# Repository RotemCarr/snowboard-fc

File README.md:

# Snowboard

Snowboard is a custom RP2350A flight controller, built to replace the flight controller in a SpeedyBee F405 V4 stack and drive its 4-in-1 ESC. This repository holds everything for it: the KiCad hardware project, the Zephyr board definition, and the firmware.

| | |
| --- | --- |
| Hardware | Rev 3, ordered from JLCPCB (fabrication and full assembly) |
| Firmware | Snowboard Rev 3 board definition (see below) |
| Zephyr | v4.4.2 |
| Hardware spec | [RFC 0001 / SNB-HW-001](docs/rfcs/0001-flight-controller-hardware.md) |
| Firmware architecture | [RFC 0002](docs/rfcs/0002-firmware-architecture.md) |

## Repository layout

```
snowboard-fc/
├── west.yml                # west manifest: pins Zephyr and its modules
├── zephyr/module.yml       # registers this repo as a Zephyr module
├── boards/snowboard/       # Zephyr board definition (snowboard/rp2350a/m33)
├── app/                    # firmware application (becomes apps/fc, RFC 0002 §2.2)
├── hardware/               # KiCad project, fab outputs, pin map, schematic PDF
└── docs/rfcs/              # design records
```

RFC 0002 adds `apps/bringup/` (self-test firmware), `drivers/` (DShot, CRSF), `dts/bindings/` and `lib/fc/` (flight logic) as they are written.

## Getting started

### Prerequisites

- [Zephyr's host dependencies](https://docs.zephyrproject.org/latest/develop/getting_started/index.html) and the Zephyr SDK
- `west` (`pip install west`)

### Set up a workspace

This repository is the manifest of a west workspace. Zephyr and its modules are fetched next to it and are not part of the repository.

```sh
west init -m https://github.com/RotemCarr/snowboard-fc.git snowboard-workspace
cd snowboard-workspace
west update
pip install -r zephyr/scripts/requirements.txt
west zephyr-export
```

The result:

```
snowboard-workspace/
├── snowboard-fc/     # this repository
├── zephyr/
├── modules/
└── build/
```

### Build

From the workspace root:

```sh
west build -b snowboard/rp2350a/m33 snowboard-fc/apps/fc
```

### Flash

Hold BOOTSEL while connecting USB, so the RP2350 mounts as a drive, then:

```sh
west flash -r uf2
```

With a Raspberry Pi Debug Probe on the SWD connector (J4), use `west flash -r probe-rs` or `west flash -r openocd`; `west debug` works the same way.

The board definition in `boards/snowboard/` describes Snowboard Rev 3 itself, following `hardware/docs/pinmap.md`: the ICM-42688 IMU on SPI0, the CRSF receiver on UART0 (J3), the battery, current and RSSI ADC channels, the status LED, buzzer and RGB LED, and the aux UART (PIO2) and I2C pads. The console is on USB (CDC ACM). DShot, the CRSF receiver node and flash partitions are still TODO in `snowboard.dtsi`; they are added with their drivers.

## Testing

Unit tests live in `tests/` and run on Zephyr's `native_sim` board, built with the host GCC, so no Zephyr SDK or hardware is needed. The `Dockerfile` provides the environment for this.

### Build the image

From the workspace root:

```sh
docker build -t snowboard-sim \
  --build-arg ZEPHYR_REF=v4.5.0 \
  --build-arg UID=$(id -u) --build-arg GID=$(id -g) \
  snowboard-fc
```

`ZEPHYR_REF` selects which Zephyr revision's Python requirements are installed and should match the revision in `west.yml`. `UID` and `GID` make files written to the mounted workspace belong to you.

### Run the tests

Start a container from the workspace root, which is mounted at `/workspace`. The named `snowboard-ccache` volume keeps the compiler cache between runs:

```sh
docker run --rm -it \
  -v "$PWD":/workspace \
  -v snowboard-ccache:/home/dev/.ccache \
  snowboard-sim
```

Inside the container, run every test suite with Twister:

```sh
west twister -T snowboard-fc/tests -p native_sim/native/64 --inline-logs
```

Twister finds each suite by its `testcase.yaml`, builds it, runs it and reports the results. To run one scenario, select it by the name in its `testcase.yaml`:

```sh
west twister -T snowboard-fc/tests -p native_sim/native/64 -s lib.fc.arming
```

Results are written to `twister-out/` in the workspace root; earlier runs are kept as `twister-out.1`, `twister-out.2` and so on. `twister-out/twister.json` holds the full report, and each suite's build directory, including its `handler.log`, is under `twister-out/`.

To browse the results, run `tools/twister-dashboard/serve.sh` on the host from the workspace root. It opens a local dashboard of every `twister-out*` run.

## Hardware

Open `hardware/snowboard_fc.kicad_pro` in KiCad 7 or newer. `hardware/README.md` covers the board, its RP2350 core (copied from Raspberry Pi's Minimal design), ordering, and planned changes for the next revision.

| File | Content |
| --- | --- |
| `hardware/docs/schematic-rev3.pdf` | All schematic sheets |
| `hardware/docs/pinmap.md` | RP2350A pin map, generated from the schematic |
| `hardware/fab/rev3/` | Files exactly as ordered from JLCPCB |

## Conventions

- **Pin changes** update the schematic, `EXPECTED` in `hardware/tools/gen_pinmap.py`, the board devicetree and SNB-HW-001 section 7 in one commit. Regenerate the pin map with `python3 tools/gen_pinmap.py` from `hardware/`; it fails if the schematic and the expected assignments disagree.
- **Design decisions** go into a new RFC in `docs/rfcs/`, numbered sequentially. Accepted RFCs are not rewritten; a later RFC supersedes them.
- **Tags** are prefixed by kind: `hw-rev3` for a hardware revision as ordered, `fw-v0.1.0` for a firmware release.
- **Zephyr is never modified in place.** Patches go to a fork referenced from `west.yml`, or into this repository as patch files applied with `west patch`.
- **Flight safety:** firmware never writes flash while armed, and test-only capabilities (such as spinning motors from the shell) exist only in the bring-up app.

## Licence

The RP2350 core block in the hardware design is derived from Raspberry Pi's RP2350A Minimal design under the MIT licence; see `hardware/LICENSE-RaspberryPi-RP2350-Minimal.txt`. No licence has been chosen yet for the rest of this repository.

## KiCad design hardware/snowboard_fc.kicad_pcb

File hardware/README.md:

# Snowboard Rev 3: RP2350A flight controller

KiCad 7 project (`snowboard_fc`) for Snowboard, a 40 × 40 mm RP2350A flight controller that replaces the flight controller in a SpeedyBee F405 V4 stack. Open `snowboard_fc.kicad_pro` in KiCad 7 or newer.

The hardware specification is **SNB-HW-001**. Where it and the schematic disagree, the schematic governs.

## Status

| Item | State |
| --- | --- |
| Revision | Rev 3, ordered from JLCPCB (fabrication and full assembly) |
| Schematic | Hierarchical, 7 sheets: top level, Power, MCU, IMU, USB, IO, LEDs |
| PCB | Fully routed. DRC (`fab/rev3/drc_report.txt`, 2026-10-13): 0 violations, 0 unconnected, 0 footprint errors |
| Schematic ↔ PCB | Every pad carries the net the schematic gives it; values and footprints match |
| Pin map | `docs/pinmap.md`, generated from the netlist and checked against SNB-HW-001 section 7 |

## Contents

```
hardware/
├── snowboard_fc.kicad_pro          # open this
├── snowboard_fc.kicad_sch          # root sheet (block diagram)
├── snowboard_fc.kicad_pcb
├── sheets/                         # power, mcu, imu, usb, io, leds
├── sym-lib-table, fp-lib-table     # project libraries via ${KIPRJMOD}/lib
├── lib/
│   ├── snowboard_fc.kicad_sym
│   └── snowboard_fc.pretty/
├── fab/
│   └── rev3/                       # exactly what was sent to JLCPCB, plus its DRC report
├── docs/
│   ├── schematic-rev3.pdf          # all 7 sheets
│   ├── pinmap.md                   # generated, see below
│   └── snowboard_fc_pcb_layers.png
├── tools/
│   ├── gen_pinmap.py               # maintained
│   └── build/                      # archival scripts used to build Rev 3 (hardcoded paths, not runnable as-is)
└── LICENSE-RaspberryPi-RP2350-Minimal.txt
```

Power symbols (`power:GND`, `power:+3V3`, `power:+5V`, `power:PWR_FLAG`) come from KiCad's standard library and are cached in the schematic. 3D models reference KiCad's standard 3D library through `${KISYS3DMOD}`; if the 3D viewer shows parts missing in KiCad 8 or newer, define `KISYS3DMOD` under Preferences → Configure Paths, pointing at your KiCad 3D model directory. Neither affects the fab outputs.

## Board

| Item | Value |
| --- | --- |
| Size | 40 × 40 mm, 3 mm corner radius |
| Mounting | 4 × Ø4.0 mm NPTH on 30.5 × 30.5 mm (M3 grommets); copper keep-out Ø6.8 mm around each, all layers |
| Layers | 4: F.Cu signal + GND pour · In1 solid GND plane · In2 signal + +3V3 pour · B.Cu signal + GND pour |
| Thickness | 1.0 mm |
| Signal rules | 0.127 mm trace / 0.127 mm clearance, vias 0.45 / 0.25 mm |
| Power rules | 0.5 mm traces (BAT, BAT_F, +5V, +5V_BUCK, VBUS, BUCK_SW); vias 0.8 / 0.4 mm |
| Hole-to-copper | 0.2 mm; copper-to-edge 0.3 mm |
| Via-in-pad | None, except the RP2350 exposed-pad vias from Raspberry Pi's footprint |
| Parts | 98; ICs and connectors on top, most 0402 passives on the bottom |

Connectors: J1 ESC 8-pin JST-SH on the rear edge (SpeedyBee F405 V4 order), J2 USB-C on the front edge (silkscreen "FWD"), J3 receiver 4-pin JST-SH on the left edge, J4 SWD 3-pin JST-SH on the right edge, JP1–JP5 1.27 mm solder pads.

## RP2350 core

The RP2350 core block is copied from Raspberry Pi's **RP2350A Minimal design, PCB R4 / schematic S1**, under the MIT licence (`LICENSE-RaspberryPi-RP2350-Minimal.txt`, Copyright (c) 2026 Raspberry Pi Ltd).

- **Copied exactly:** the RP2350A footprint with its 9 exposed-pad vias; the core regulator (AOTA-B201610S3R3-101-T inductor L2 with its polarity dot on +1V1, 4.7 µF on VREG_VIN, the 1.1 V output and VREG_AVDD, 33 Ω AVDD resistor); all 100 nF decoupling including one per DVDD pin; the 27 Ω USB resistors; the crystal group (ABM8-272-T3, 15 pF, 1 kΩ). 114 of 114 pads, 89 of 89 tracks, 22 of 22 vias and 8 of 8 zones match the reference.
- **Fan-out:** every RP2350 pin in use escapes along Raspberry Pi's own traces to the edge of the core block. No foreign copper sits inside the regulator, crystal or under-chip zones.
- **Deliberate differences:** this board is 4-layer 1.0 mm with a solid GND plane on In1 (the reference is 2-layer 1.6 mm), and the core's GND vias land on that plane. The flash sits left of the core because the reference flash position is taken by J2.

## Ordering

Files in `fab/rev3/`: `snowboard_fc_gerbers_jlc.zip`, `snowboard_fc_JLC_BOM_v7.csv`, `snowboard_fc_JLC_CPL_v5.csv`.

- JLC settings: 4 layers, 1.0 mm, JLC04161H-7628 stackup, min track/space 0.127 mm, min hole 0.25 mm, ENIG.
- J2 (GCT USB4085-GF-A) and SW1 (C&K PTS810SJM250SMTRLFS) come through JLC Global Sourcing. L2 and Y1 may need pre-order.
- In the placement preview, check: the RP2350 pin-1 dot; L2's dot toward +1V1; D4's pin-1 mark; J1, J3 and J4 openings facing the board edge; J2 seated over its holes.

## Notes for firmware

- **Pin map:** use `docs/pinmap.md` for the board DTS and pinctrl.
- **Aux UART and ESC telemetry use PIO UARTs.** GPIO12/13 offer only UART0, which the receiver uses on GPIO0/1, and GPIO22 offers only UART1 TX.
- **D4 (XL-1615RGBC-WS2812B):** single-wire GRB at 800 kbit/s, reset low time at least 300 µs. Pinout 1 GND, 2 DIN, 3 VDD, 4 DOUT. It replaced the discontinued WS2812B-2020 in the same position.
- **IMU INT1** has no external pull-up; configure it push-pull.
- **Crystal:** the circuit is tuned for IOVDD = 3.3 V.

## Regenerating the docs

From `hardware/`:

```sh
kicad-cli sch export pdf -o docs/schematic-rev3.pdf snowboard_fc.kicad_sch
python3 tools/gen_pinmap.py
```

`gen_pinmap.py` exports the netlist itself and exits with an error if a GPIO's net no longer matches its `EXPECTED` table. When a pin moves, update the schematic, `EXPECTED`, the board DTS and SNB-HW-001 section 7 together.

## Revision history

| Revision | Summary |
| --- | --- |
| v0.3 | First fully routed board |
| v0.3.1 | Removed three vias-in-pad; moved C13, C27, C28 |
| Rev 3 | RP2350 core rebuilt as an exact copy of Raspberry Pi's Minimal R4 (regulator, crystal, decoupling, USB termination); ABM8-272-T3 crystal; AOTA inductor with polarity fixed; W25Q32JVSNIQ flash; XL-1615RGBC-WS2812B; full JLC assembly including J2; schematic title blocks set to Rev 3; project restructured into `sheets/`, `lib/`, `fab/rev3/` (connectivity and Gerbers unchanged) |

## Next revision — planned changes

Findings from checking v0.3.1 against the design intent (measured on the routed board, not assumed), ordered by how much they matter. Items 1–10 were written against v0.3.1 and are carried over unchanged; re-check each against the Rev 3 layout before acting on it, since the Rev 3 core rebuild moved the RP2350 decoupling, regulator and USB termination. Item 11 was found on Rev 3.

| # | Change | Why | How |
|---|---|---|---|
| 1 | **Move L1 (buck inductor) to sit directly on U3's SW pin; keep the switch node on F.Cu only.** | The switch node (`BUCK_SW`) is the noisiest net on the board. Today it is 13.5 mm long, drops to 0.35–0.45 mm, and changes layers through two 0.25 mm vias. Works at the real load (< 0.5 A) but radiates more than it should and is not sized for the TPS54202's 2 A rating. | Place L1 with its pin 1 pad ≤ 1.5 mm from U3 pin 2; route SW as one 0.6–0.8 mm F.Cu trace, no vias; put the 22 µF output caps and the BOOT cap in the same corner so the switching loop is small. Re-run the autorouter afterwards. |
| 2 | **Move U2 (QSPI flash) against the RP2350.** | Flash is 18 mm from the MCU; QSPI traces are 14–24 mm with 1–2 vias each. Fine at 66–100 MHz, marginal if QSPI is pushed to 133 MHz. | Place U2 within 5 mm of RP2350 pins 55–60 (top-left of the QFN) and route QSPI on F.Cu with no vias, matched within 1 mm. The USB-C sits in that space today, so either shift J2 left along the front edge or switch to a mid-mount SMD USB-C (smaller footprint). |
| 3 | **Pull the four distant RP2350 decoupling caps in.** | C2, C3, C6 and C13 are 2.8–4.8 mm from the nearest supply pin; the other seven are ≤ 1.7 mm. 100 nF decoupling is only effective within ~2 mm of the pin. | After #1 and #2 free up bottom-side space under/around the QFN, hand-place one 100 nF directly under each IOVDD pin (via-in-pad into the pin's own via is fine on the bottom side) before autorouting. |
| 4 | **Route USB D+/D− as a differential pair.** | Currently two single-ended traces, D+ 25.0 mm, D− 33.5 mm (8.5 mm skew), 4 vias, no impedance control. Acceptable for the RP2350's full-speed USB; not good practice. | Hand-route D+/D− side by side on F.Cu from U1 pins 51/52 through the 27 Ω resistors to J2, with the ESD array (D5) on the same layer, length-matched within 1 mm and no vias. Lock before autorouting. |
| 5 | **Thermal reliefs on the outer GND/+3V3 pours (if hand-soldering).** | SMD pads connect solid to the pours in v0.3.1 (chosen to clear DRC "starved thermal" errors). Solid connections make 0402 ground pads heat-sink the iron. Irrelevant for hot-plate reflow. | Set the F.Cu/B.Cu pours to thermal relief for SMD pads (gap 0.25 mm, spoke 0.3 mm), keep In1 solid, re-run DRC and fix any pad that cannot get two spokes. Can be done on v0.3.1 without re-routing. |
| 6 | **Move the IMU to the board centre and add a ground ring under it.** | U5 is 5 mm off-centre (fine for the gyro, slightly worse for the accelerometer under rotation). The SPI bus is 6–12 mm with 2–3 vias per line and no guard; fine at 24 MHz but could be tidier. | Place U5 at (0, 0) first, hand-route SCK/MOSI/MISO/CS on F.Cu over the solid In1 ground, keep other signals out of a ~3 mm ring around it, and keep the ferrite + caps on the VDD side. |
| 7 | **Replace J2 (THT USB4085) with a mid-mount or SMD USB-C.** | The through-hole receptacle blocks both sides of 9 × 9 mm and pushes the flash away (#2). | Mid-mount SMD USB-C 16-pin (e.g. GCT USB4110 or similar), slot in the board edge, footprint from the vendor drawing. |
| 8 | **Keep-out ring silkscreen and a mask-defined annulus at the grommet holes.** | Hole keep-outs are copper-only today; the silkscreen ring is informational. | Add a 7 mm solder-mask ring around each hole so the grommet flange never sits on exposed copper. |
| 9 | **Verify the ICM-42688-P land pattern against DS-000347 §10.2.** | The footprint is the generic LGA-14 2.5 × 3.0 / 0.5 mm pattern (correct pad order per the datasheet pinout figure), not the vendor-drawn one. | Compare pad size/pitch with the datasheet drawing before fab; adjust if different. |
| 10 | **Power-via sizing on BAT_F / +5V.** | A few power nets change layers through single 0.25 mm vias; adequate below ~0.8 A, not for the full 2 A buck rating. | Use 0.8/0.4 mm vias (already defined in the Power netclass) or 2–3 vias in parallel wherever a power net changes layer. |
| 11 | **Move the aux UART pads (JP1) from GPIO12/13 to GPIO20/21, and ESC telemetry to a UART RX pin.** | GPIO12/13 offer only UART0, which the receiver already uses on GPIO0/1, and GPIO22 offers only UART1 TX. Rev 3 works around this with PIO UARTs in firmware (SNB-HW-001 L-07). JP1's value still reads "UART1 pads". | Route JP1 TX/RX to GPIO20/21 (UART1 TX/RX, both unused). Move ESC_TEL to GPIO23 (UART1 RX, alternate function) only if the aux UART goes elsewhere; otherwise keep TEL on a PIO UART. Update `EXPECTED` in `tools/gen_pinmap.py` and the board DTS in the same commit. |

Items 5 and 10 can be applied to v0.3.1 without re-placing anything. Items 1–4, 6 and 7 change placement and need a fresh autoroute, which the `tools/` scripts do end to end.

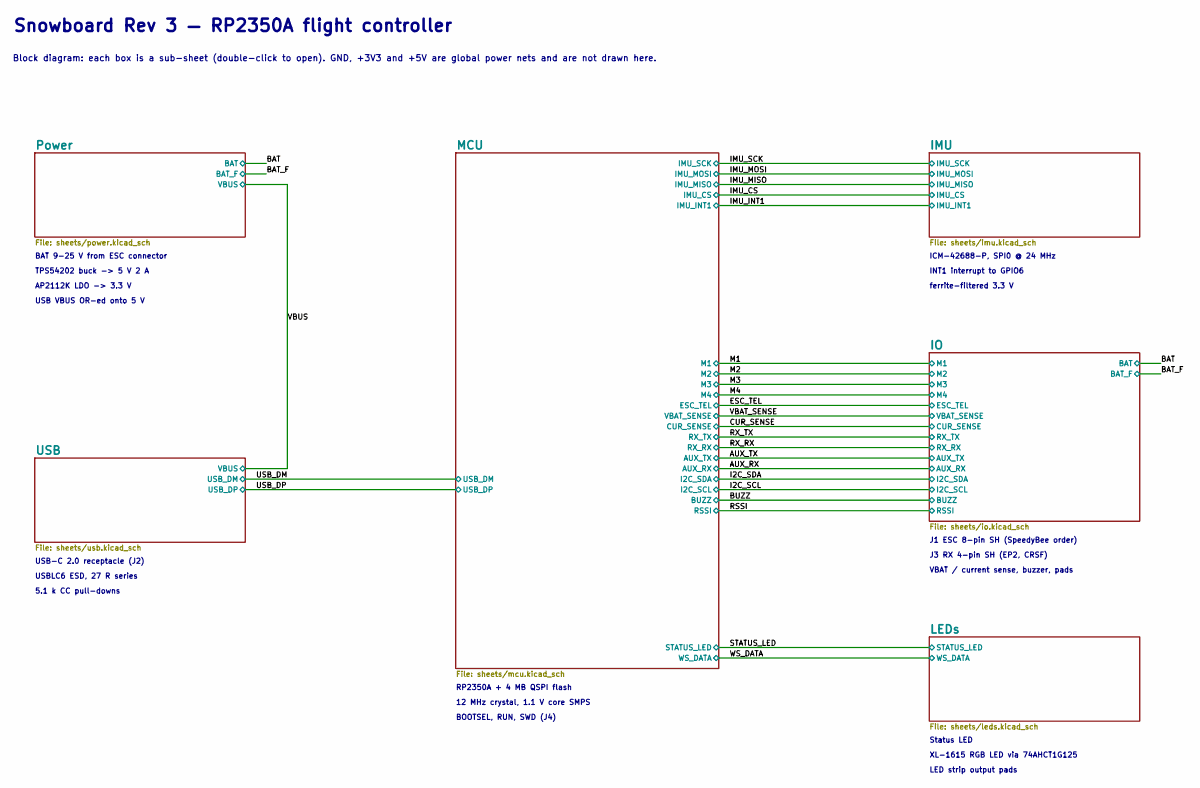
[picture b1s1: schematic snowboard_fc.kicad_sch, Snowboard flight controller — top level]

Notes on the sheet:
Snowboard Rev 3 — RP2350A flight controller
Block diagram: each box is a sub-sheet (double-click to open). GND, +3V3 and +5V are global power nets and are not drawn here.
BAT 9-25 V from ESC connector
TPS54202 buck -> 5 V 2 A
AP2112K LDO -> 3.3 V
USB VBUS OR-ed onto 5 V
RP2350A + 4 MB QSPI flash
12 MHz crystal, 1.1 V core SMPS
BOOTSEL, RUN, SWD (J4)
ICM-42688-P, SPI0 @ 24 MHz
INT1 interrupt to GPIO6
ferrite-filtered 3.3 V
USB-C 2.0 receptacle (J2)
USBLC6 ESD, 27 R series
5.1 k CC pull-downs
J1 ESC 8-pin SH (SpeedyBee order)
J3 RX 4-pin SH (EP2, CRSF)
VBAT / current sense, buzzer, pads
Status LED
XL-1615 RGB LED via 74AHCT1G125
LED strip output pads

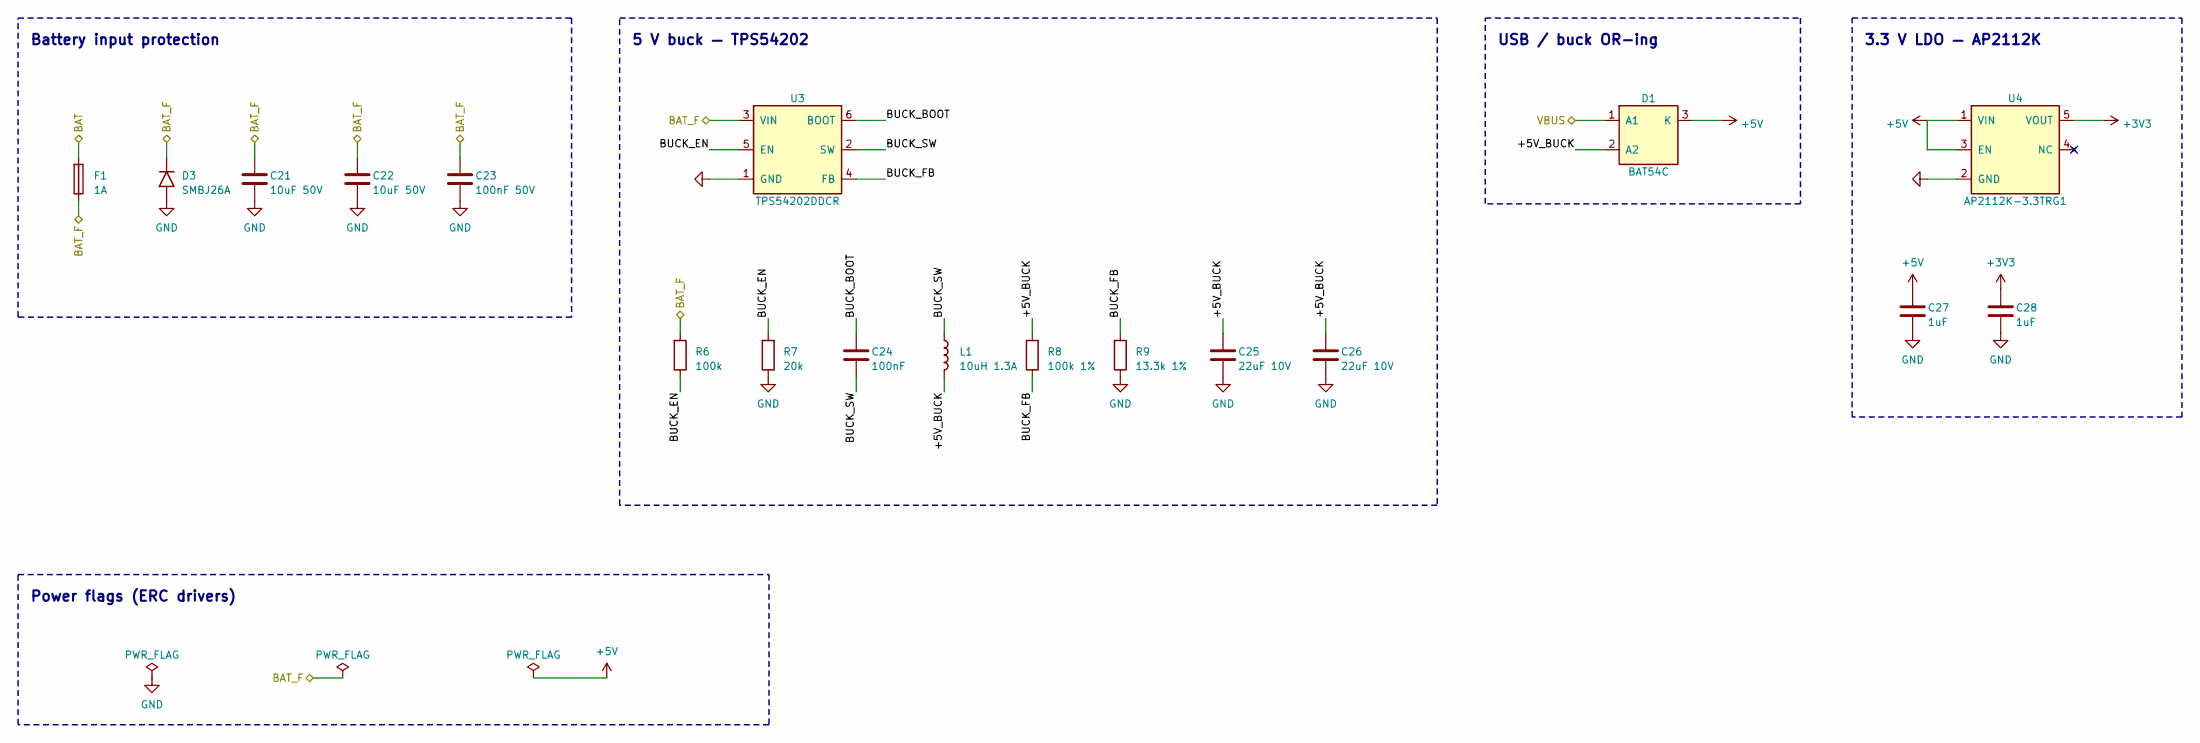
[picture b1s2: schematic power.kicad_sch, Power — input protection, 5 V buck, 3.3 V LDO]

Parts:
C21, C22: 10uF 50V; C_1210_3225Metric; LCSC C5156756
C23: 100nF 50V; C_0402_1005Metric; LCSC C307331
C24: 100nF; C_0402_1005Metric; LCSC C1525
C25, C26: 22uF 10V; C_0805_2012Metric; LCSC C45783
C27, C28: 1uF; C_0402_1005Metric; LCSC C52923
D1: BAT54C; SOT-23; MPN BAT54C; LCSC C22466350
D3: SMBJ26A; D_SMB; MPN SMBJ26A (Littelfuse); LCSC C3019963
F1: 1A; Fuse_1206_3216Metric; MPN F12F1 (TLC); LCSC C2924985
L1: 10uH 1.3A; L_Taiyo-Yuden_NR-40xx; MPN YNR4018-100M (YJYCOIN); LCSC C340371
R6: 100k; R_0402_1005Metric; LCSC C25741
R7: 20k; R_0402_1005Metric; LCSC C25765
R8: 100k 1%; R_0402_1005Metric; LCSC C25741
R9: 13.3k 1%; R_0402_1005Metric; LCSC C122547
U3: TPS54202DDCR; SOT-23-6; MPN TPS54202DDCR (TI); LCSC C2070672
U4: AP2112K-3.3TRG1; SOT-23-5; MPN AP2112K-3.3TRG1 (Diodes Inc); LCSC C51118

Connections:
+3V3: C28.1, U4.5 (VOUT); also elsewhere on the board
+5V: C27.1, D1.3 (K), U4.1 (VIN), U4.3 (EN); also elsewhere on the board
/BAT: F1.1; also elsewhere on the board
/BAT_F: C21.1, C22.1, C23.1, D3.1, F1.2, R6.1, U3.3 (VIN); also elsewhere on the board
/Power/+5V_BUCK: C25.1, C26.1, D1.2 (A2), L1.2, R8.1
/Power/BUCK_BOOT: C24.1, U3.6 (BOOT)
/Power/BUCK_EN: R6.2, R7.1, U3.5 (EN)
/Power/BUCK_FB: R8.2, R9.1, U3.4 (FB)
/Power/BUCK_SW: C24.2, L1.1, U3.2 (SW)
/VBUS: D1.1 (A1); also elsewhere on the board
GND: C21.2, C22.2, C23.2, C25.2, C26.2, C27.2, C28.2, D3.2, R7.2, R9.2, U3.1 (GND), U4.2 (GND); also elsewhere on the board

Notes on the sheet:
Battery input protection
5 V buck — TPS54202
USB / buck OR-ing
3.3 V LDO — AP2112K
Power flags (ERC drivers)

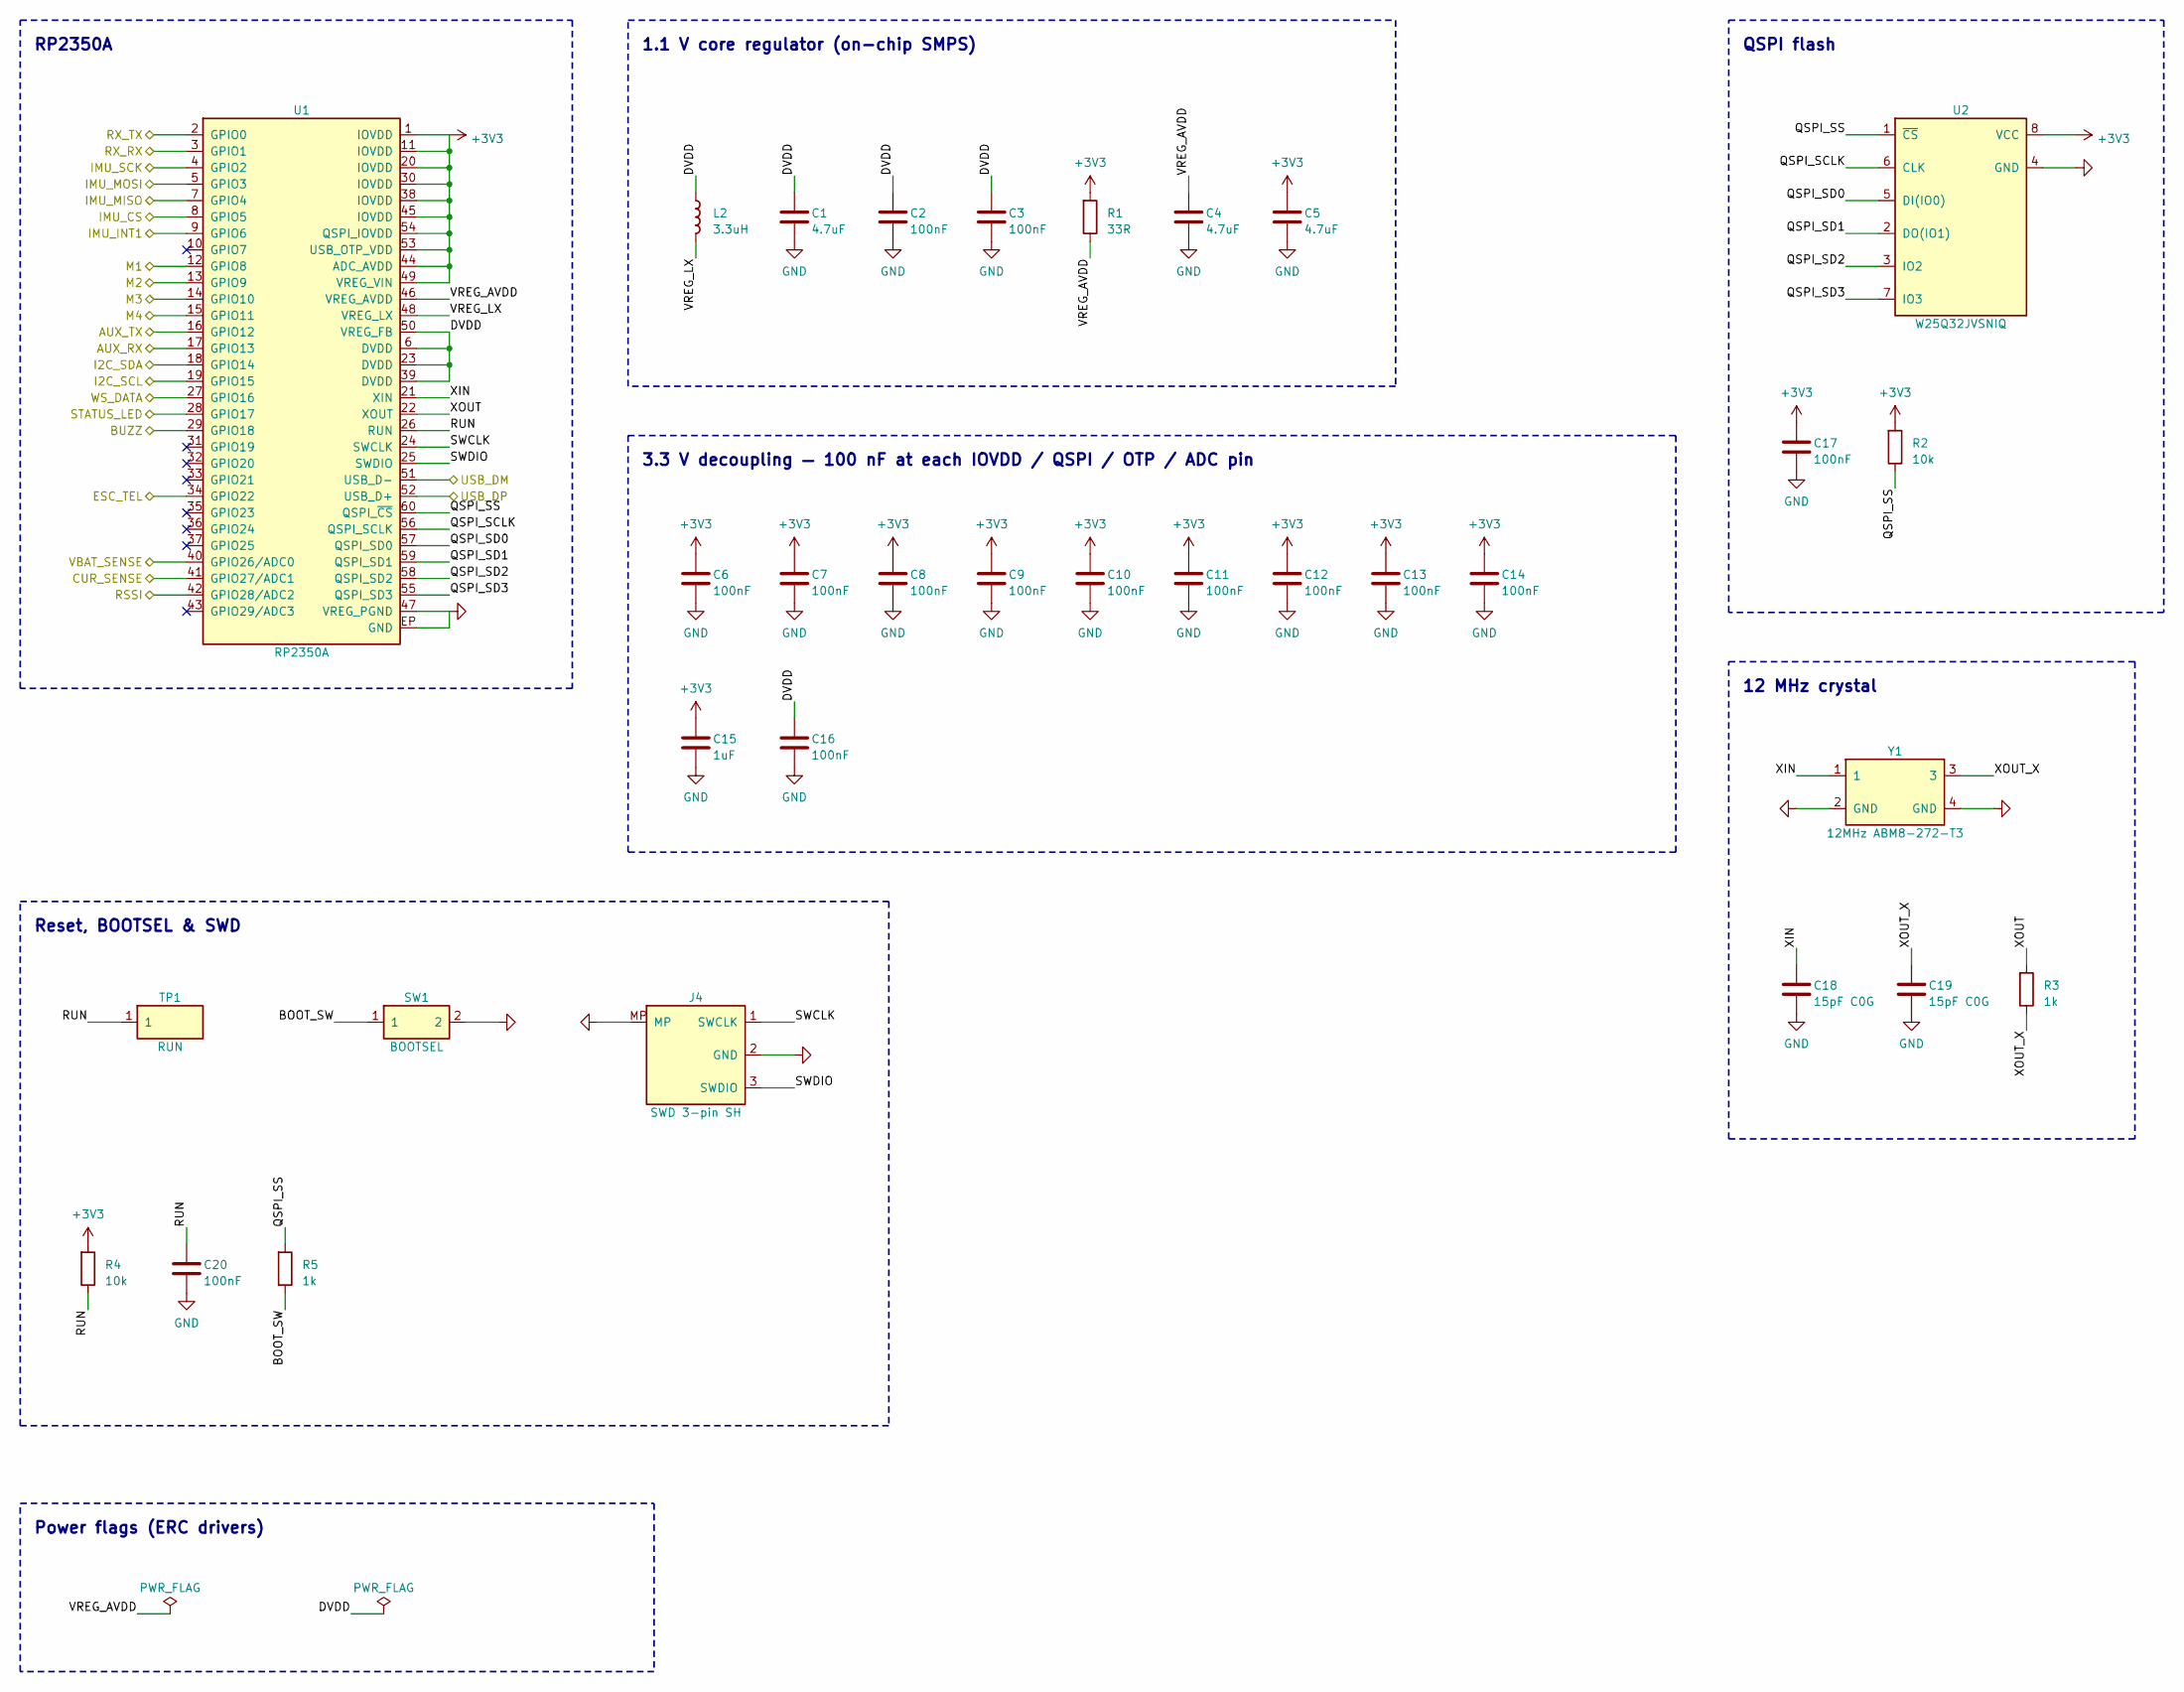
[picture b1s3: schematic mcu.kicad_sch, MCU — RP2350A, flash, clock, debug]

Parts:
C1, C5: 4.7uF; RPI_C_0402_capc1005x50_wide; LCSC C23733
C2, C3, C6, C7, C8, C9, C10, C11, C12, C16: 100nF; RPI_C_0402_capc1005x50; LCSC C1525
C4: 4.7uF; RPI_C_0402_capc1005x50; LCSC C23733
C13, C14, C17, C20: 100nF; C_0402_1005Metric; LCSC C1525
C15: 1uF; C_0402_1005Metric; LCSC C52923
C18, C19: 15pF C0G; RPI_C_0402_capc1005x50; LCSC C1548
J4: SWD 3-pin SH; JST_SH_SM03B-SRSS-TB_1x03-1MP_P1.00mm_Horizontal; MPN SM03B-SRSS-TB (JST)
L2: 3.3uH; RPI_L_AOTA-B201610S3R3-101-T; MPN AOTA-B201610S3R3-101-T (Abracon); LCSC C42411119
R1: 33R; RPI_R_0402_resc1005x35; LCSC C25105
R2, R4: 10k; R_0402_1005Metric; LCSC C25744
R3: 1k; RPI_R_0402_resc1005x35; LCSC C11702
R5: 1k; R_0402_1005Metric; LCSC C11702
SW1: BOOTSEL; SW_SPST_PTS810; MPN PTS810SJM250SMTRLFS (C&K)
TP1: RUN; TestPoint_Pad_1.0x1.0mm
U1: RP2350A; RPI_RP2350A_QFN60_vias; MPN RP2350A (Raspberry Pi); LCSC C42411118
U2: W25Q32JVSNIQ; SOIC-8_3.9x4.9mm_P1.27mm; MPN W25Q32JVSNIQ (Winbond); LCSC C5355146
Y1: 12MHz ABM8-272-T3; RPI_XTAL_3225_ABM8; MPN ABM8-272-T3 (Abracon); LCSC C20625731

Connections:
+3V3: C5.1, C6.1, C7.1, C8.1, C9.1, C10.1, C11.1, C12.1, C13.1, C14.1, C15.1, C17.1, R1.1, R2.1, R4.1, U1.1 (IOVDD), U1.11 (IOVDD), U1.20 (IOVDD), U1.30 (IOVDD), U1.38 (IOVDD), U1.44 (ADC_AVDD), U1.45 (IOVDD), U1.49 (VREG_VIN), U1.53 (USB_OTP_VDD), U1.54 (QSPI_IOVDD), U2.8 (VCC); also elsewhere on the board
/AUX_RX: U1.17 (GPIO13); also elsewhere on the board
/AUX_TX: U1.16 (GPIO12); also elsewhere on the board
/BUZZ: U1.29 (GPIO18); also elsewhere on the board
/CUR_SENSE: U1.41 (GPIO27/ADC1); also elsewhere on the board
/ESC_TEL: U1.34 (GPIO22); also elsewhere on the board
/I2C_SCL: U1.19 (GPIO15); also elsewhere on the board
/I2C_SDA: U1.18 (GPIO14); also elsewhere on the board
/IMU_CS: U1.8 (GPIO5); also elsewhere on the board
/IMU_INT1: U1.9 (GPIO6); also elsewhere on the board
/IMU_MISO: U1.7 (GPIO4); also elsewhere on the board
/IMU_MOSI: U1.5 (GPIO3); also elsewhere on the board
/IMU_SCK: U1.4 (GPIO2); also elsewhere on the board
/M1: U1.12 (GPIO8); also elsewhere on the board
/M2: U1.13 (GPIO9); also elsewhere on the board
/M3: U1.14 (GPIO10); also elsewhere on the board
/M4: U1.15 (GPIO11); also elsewhere on the board
/MCU/BOOT_SW: R5.2, SW1.1
/MCU/DVDD: C1.1, C2.1, C3.1, C16.1, L2.1, U1.6 (DVDD), U1.23 (DVDD), U1.39 (DVDD), U1.50 (VREG_FB)
/MCU/QSPI_SCLK: U1.56 (QSPI_SCLK), U2.6 (CLK)
/MCU/QSPI_SD0: U1.57 (QSPI_SD0), U2.5 (DI(IO0))
/MCU/QSPI_SD1: U1.59 (QSPI_SD1), U2.2 (DO(IO1))
/MCU/QSPI_SD2: U1.58 (QSPI_SD2), U2.3 (IO2)
/MCU/QSPI_SD3: U1.55 (QSPI_SD3), U2.7 (IO3)
/MCU/QSPI_SS: R2.2, R5.1, U1.60 (QSPI_~CS), U2.1 (~CS)
/MCU/RUN: C20.1, R4.2, TP1.1, U1.26 (RUN)
/MCU/SWCLK: J4.1 (SWCLK), U1.24 (SWCLK)
/MCU/SWDIO: J4.3 (SWDIO), U1.25 (SWDIO)
/MCU/VREG_AVDD: C4.1, R1.2, U1.46 (VREG_AVDD)
/MCU/VREG_LX: L2.2, U1.48 (VREG_LX)
/MCU/XIN: C18.1, U1.21 (XIN), Y1.1
/MCU/XOUT: R3.1, U1.22 (XOUT)
/MCU/XOUT_X: C19.1, R3.2, Y1.3
/RSSI: U1.42 (GPIO28/ADC2); also elsewhere on the board
/RX_RX: U1.3 (GPIO1); also elsewhere on the board
/RX_TX: U1.2 (GPIO0); also elsewhere on the board
/STATUS_LED: U1.28 (GPIO17); also elsewhere on the board
/USB_DM: U1.51 (USB_D-); also elsewhere on the board
/USB_DP: U1.52 (USB_D+); also elsewhere on the board
/VBAT_SENSE: U1.40 (GPIO26/ADC0); also elsewhere on the board
/WS_DATA: U1.27 (GPIO16); also elsewhere on the board
GND: C1.2, C2.2, C3.2, C4.2, C5.2, C6.2, C7.2, C8.2, C9.2, C10.2, C11.2, C12.2, C13.2, C14.2, C15.2, C16.2, C17.2, C18.2, C19.2, C20.2, J4.2 (GND), J4.MP, SW1.2, U1.47 (VREG_PGND), U1.EP (GND), U2.4 (GND), Y1.2 (GND), Y1.4 (GND); also elsewhere on the board

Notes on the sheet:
RP2350A
1.1 V core regulator (on-chip SMPS)
3.3 V decoupling — 100 nF at each IOVDD / QSPI / OTP / ADC pin
QSPI flash
12 MHz crystal
Reset, BOOTSEL & SWD
Power flags (ERC drivers)

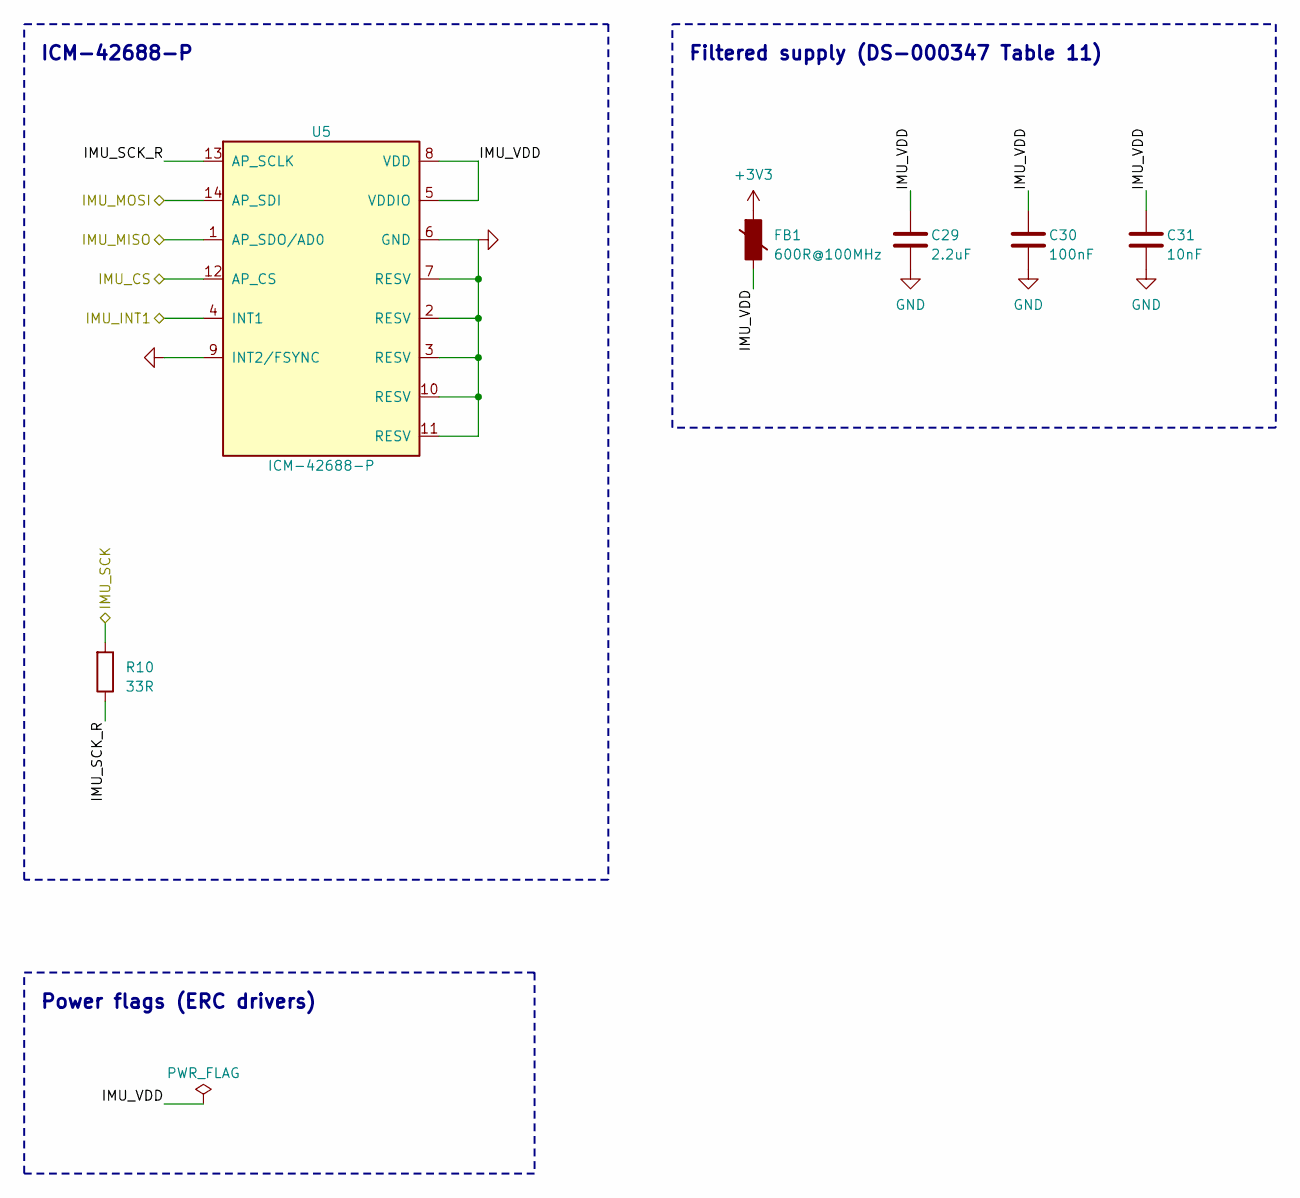
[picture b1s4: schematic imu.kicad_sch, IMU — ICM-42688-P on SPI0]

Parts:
C29: 2.2uF; C_0603_1608Metric; LCSC C23630
C30: 100nF; C_0402_1005Metric; LCSC C1525
C31: 10nF; C_0402_1005Metric; MPN C0402C103J5RAC7867 (KEMET); LCSC C696350
FB1: 600R@100MHz; L_0603_1608Metric; MPN GZ1608D601TF (Sunlord); LCSC C1002
R10: 33R; R_0402_1005Metric; LCSC C25105
U5: ICM-42688-P; ICM-42688-P_LGA-14_2.5x3.0mm_P0.5mm; MPN ICM-42688-P (TDK InvenSense); LCSC C1850418

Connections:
+3V3: FB1.1; also elsewhere on the board
/IMU/IMU_SCK_R: R10.2, U5.13 (AP_SCLK)
/IMU/IMU_VDD: C29.1, C30.1, C31.1, FB1.2, U5.5 (VDDIO), U5.8 (VDD)
/IMU_CS: U5.12 (AP_CS); also elsewhere on the board
/IMU_INT1: U5.4 (INT1); also elsewhere on the board
/IMU_MISO: U5.1 (AP_SDO/AD0); also elsewhere on the board
/IMU_MOSI: U5.14 (AP_SDI); also elsewhere on the board
/IMU_SCK: R10.1; also elsewhere on the board
GND: C29.2, C30.2, C31.2, U5.2 (RESV), U5.3 (RESV), U5.6 (GND), U5.7 (RESV), U5.9 (INT2/FSYNC), U5.10 (RESV), U5.11 (RESV); also elsewhere on the board

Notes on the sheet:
ICM-42688-P
Filtered supply (DS-000347 Table 11)
Power flags (ERC drivers)

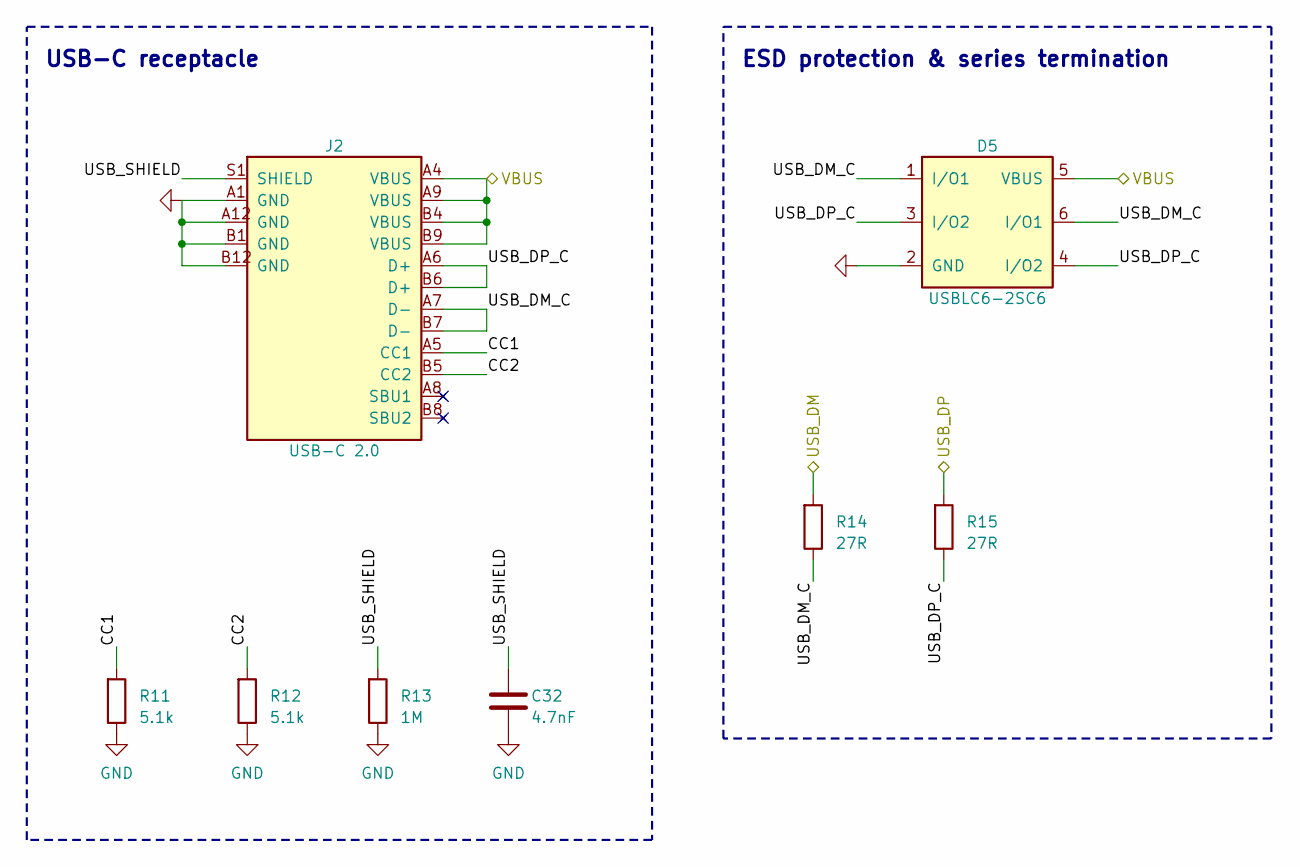
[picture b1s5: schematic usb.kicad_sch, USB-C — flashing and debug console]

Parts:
C32: 4.7nF; C_0402_1005Metric; LCSC C1538
D5: USBLC6-2SC6; SOT-23-6; MPN USBLC6-2SC6 (ST); LCSC C7519
J2: USB-C 2.0; USB_C_Receptacle_GCT_USB4085-GF-A; MPN USB4085-GF-A (GCT)
R11, R12: 5.1k; R_0402_1005Metric; LCSC C25905
R13: 1M; R_0402_1005Metric; LCSC C26083
R14, R15: 27R; RPI_R_0402_resc1005x35; LCSC C25100

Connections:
/USB/CC1: J2.A5 (CC1), R11.1
/USB/CC2: J2.B5 (CC2), R12.1
/USB/USB_DM_C: D5.1 (I/O1), D5.6 (I/O1), J2.A7 (D-), J2.B7 (D-), R14.2
/USB/USB_DP_C: D5.3 (I/O2), D5.4 (I/O2), J2.A6 (D+), J2.B6 (D+), R15.2
/USB/USB_SHIELD: C32.1, J2.S1 (SHIELD), R13.1
/USB_DM: R14.1; also elsewhere on the board
/USB_DP: R15.1; also elsewhere on the board
/VBUS: D5.5 (VBUS), J2.A4 (VBUS), J2.A9 (VBUS), J2.B4 (VBUS), J2.B9 (VBUS); also elsewhere on the board
GND: C32.2, D5.2 (GND), J2.A1 (GND), J2.A12 (GND), J2.B1 (GND), J2.B12 (GND), R11.2, R12.2, R13.2; also elsewhere on the board

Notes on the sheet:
USB-C receptacle
ESD protection & series termination

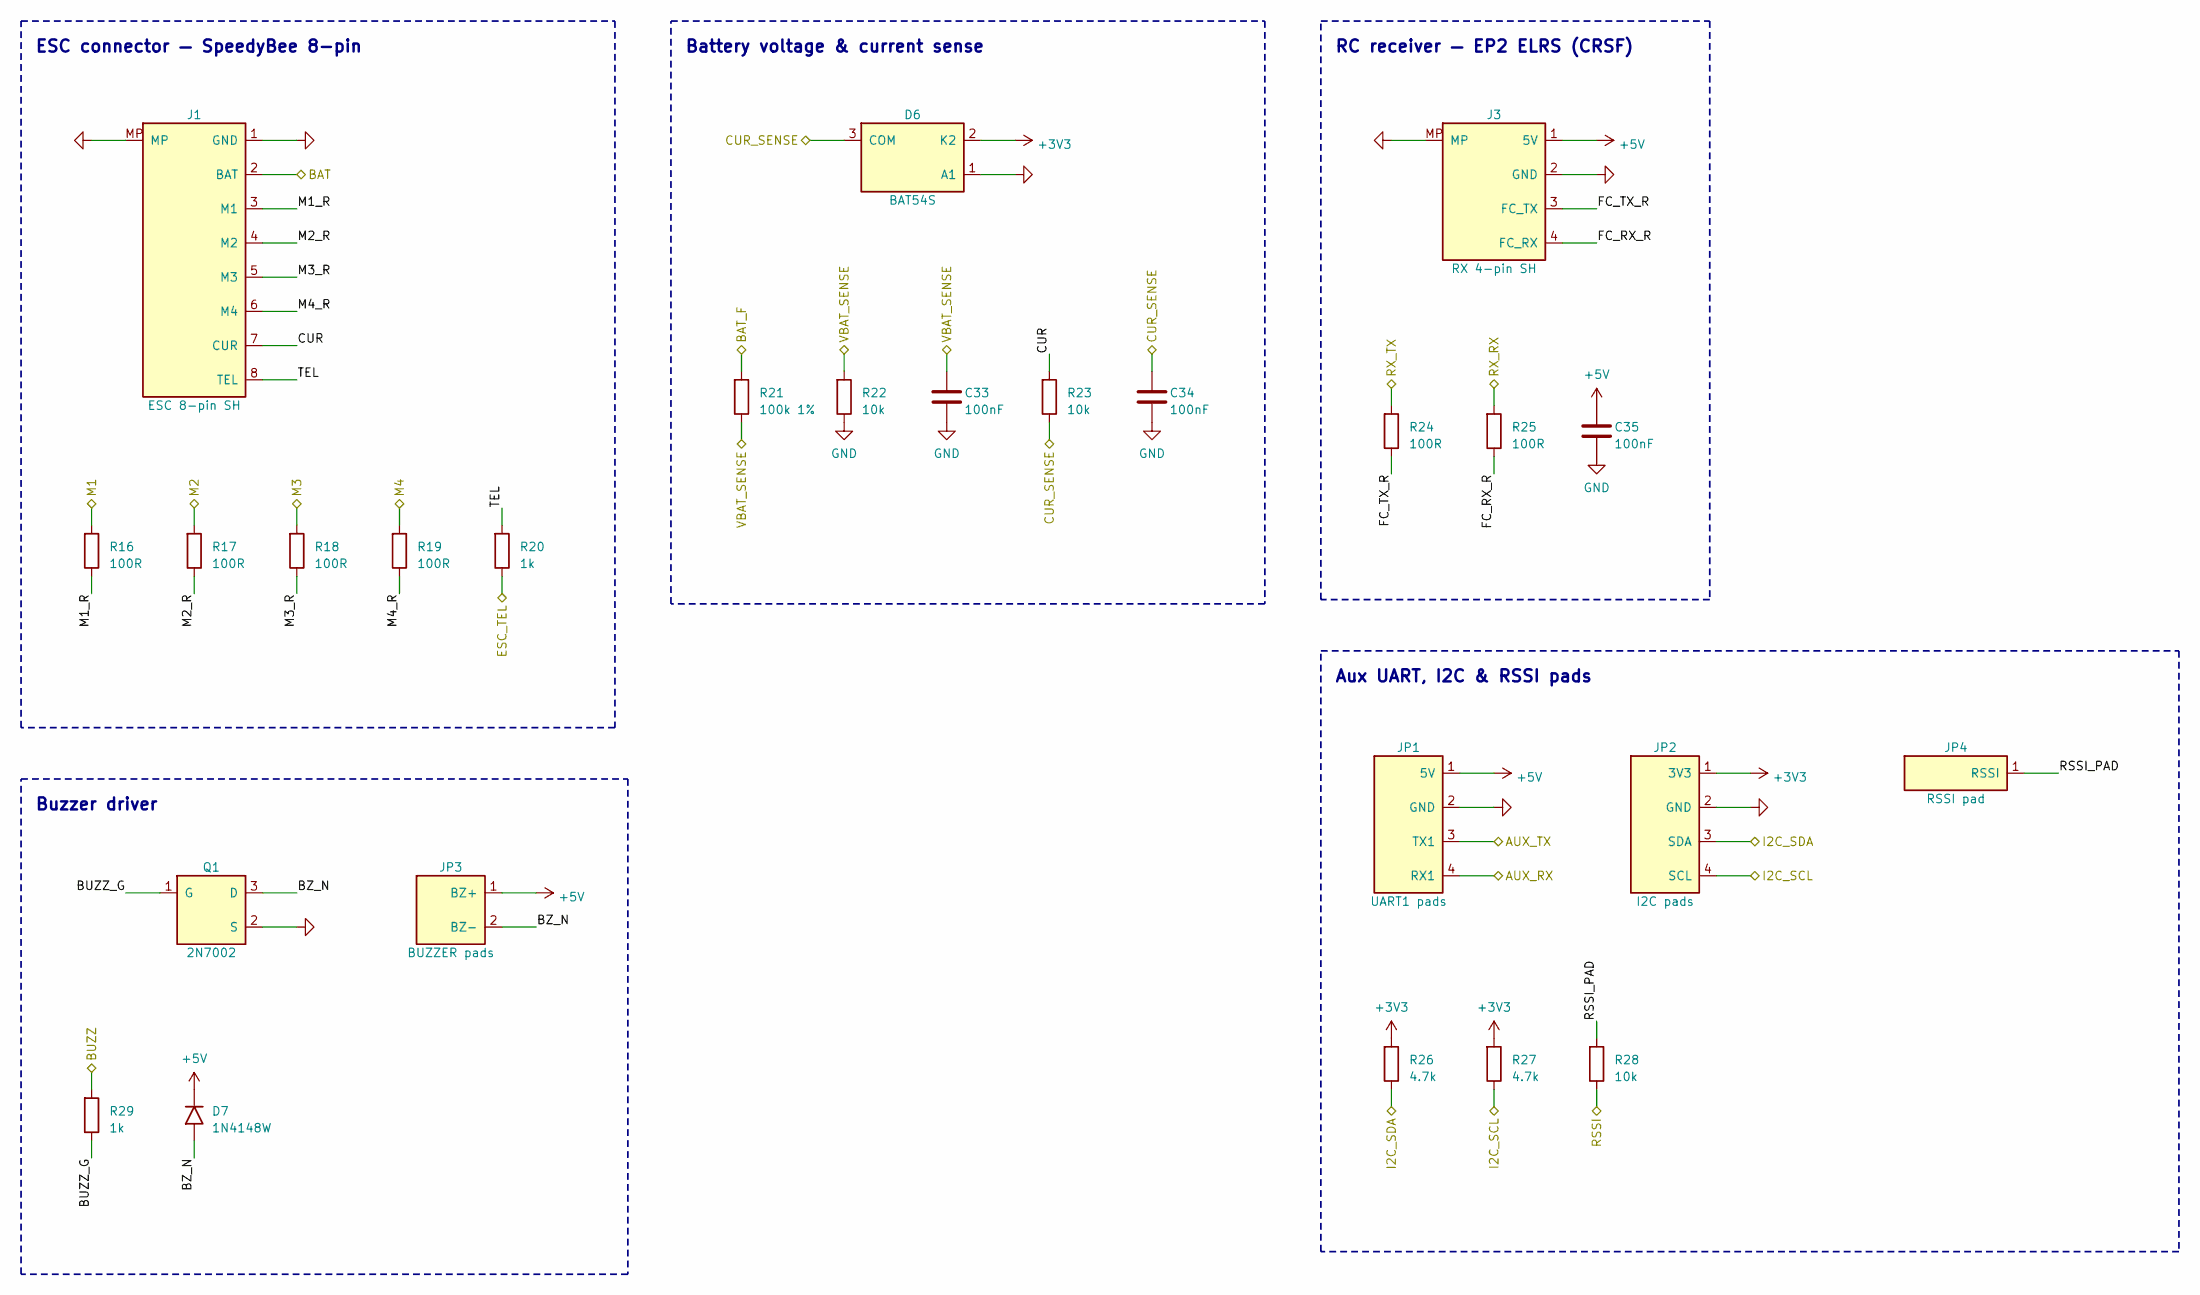
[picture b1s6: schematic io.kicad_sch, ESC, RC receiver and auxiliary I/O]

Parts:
C33, C34, C35: 100nF; C_0402_1005Metric; LCSC C1525
D6: BAT54S; SOT-23; MPN BAT54S; LCSC C7420333
D7: 1N4148W; D_SOD-123; MPN 1N4148W; LCSC C81598
J1: ESC 8-pin SH; JST_SH_SM08B-SRSS-TB_1x08-1MP_P1.00mm_Horizontal; MPN SM08B-SRSS-TB (JST)
J3: RX 4-pin SH; JST_SH_SM04B-SRSS-TB_1x04-1MP_P1.00mm_Horizontal; MPN SM04B-SRSS-TB (JST)
JP1: UART1 pads; PinHeader_1x04_P1.27mm_Vertical
JP2: I2C pads; PinHeader_1x04_P1.27mm_Vertical
JP3: BUZZER pads; PinHeader_1x02_P1.27mm_Vertical
JP4: RSSI pad; PinHeader_1x01_P1.27mm_Vertical
Q1: 2N7002; SOT-23; MPN 2N7002; LCSC C8545
R16, R17, R18, R19, R24, R25: 100R; R_0402_1005Metric; LCSC C25076
R20, R29: 1k; R_0402_1005Metric; LCSC C11702
R21: 100k 1%; R_0402_1005Metric; LCSC C25741
R22, R23, R28: 10k; R_0402_1005Metric; LCSC C25744
R26, R27: 4.7k; R_0402_1005Metric; LCSC C25900

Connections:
+3V3: D6.2 (K2), JP2.1 (3V3), R26.1, R27.1; also elsewhere on the board
+5V: C35.1, D7.1, J3.1 (5V), JP1.1 (5V), JP3.1 (BZ+); also elsewhere on the board
/AUX_RX: JP1.4 (RX1); also elsewhere on the board
/AUX_TX: JP1.3 (TX1); also elsewhere on the board
/BAT: J1.2 (BAT); also elsewhere on the board
/BAT_F: R21.1; also elsewhere on the board
/BUZZ: R29.1; also elsewhere on the board
/CUR_SENSE: C34.1, D6.3 (COM), R23.2; also elsewhere on the board
/ESC_TEL: R20.2; also elsewhere on the board
/I2C_SCL: JP2.4 (SCL), R27.2; also elsewhere on the board
/I2C_SDA: JP2.3 (SDA), R26.2; also elsewhere on the board
/IO/BUZZ_G: Q1.1 (G), R29.2
/IO/BZ_N: D7.2, JP3.2 (BZ-), Q1.3 (D)
/IO/CUR: J1.7 (CUR), R23.1
/IO/FC_RX_R: J3.4 (FC_RX), R25.2
/IO/FC_TX_R: J3.3 (FC_TX), R24.2
/IO/M1_R: J1.3 (M1), R16.2
/IO/M2_R: J1.4 (M2), R17.2
/IO/M3_R: J1.5 (M3), R18.2
/IO/M4_R: J1.6 (M4), R19.2
/IO/RSSI_PAD: JP4.1, R28.1
/IO/TEL: J1.8 (TEL), R20.1
/M1: R16.1; also elsewhere on the board
/M2: R17.1; also elsewhere on the board
/M3: R18.1; also elsewhere on the board
/M4: R19.1; also elsewhere on the board
/RSSI: R28.2; also elsewhere on the board
/RX_RX: R25.1; also elsewhere on the board
/RX_TX: R24.1; also elsewhere on the board
/VBAT_SENSE: C33.1, R21.2, R22.1; also elsewhere on the board
GND: C33.2, C34.2, C35.2, D6.1 (A1), J1.1 (GND), J1.MP, J3.2 (GND), J3.MP, JP1.2 (GND), JP2.2 (GND), Q1.2 (S), R22.2; also elsewhere on the board

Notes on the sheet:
ESC connector — SpeedyBee 8-pin
Battery voltage & current sense
RC receiver — EP2 ELRS (CRSF)
Aux UART, I2C & RSSI pads
Buzzer driver
